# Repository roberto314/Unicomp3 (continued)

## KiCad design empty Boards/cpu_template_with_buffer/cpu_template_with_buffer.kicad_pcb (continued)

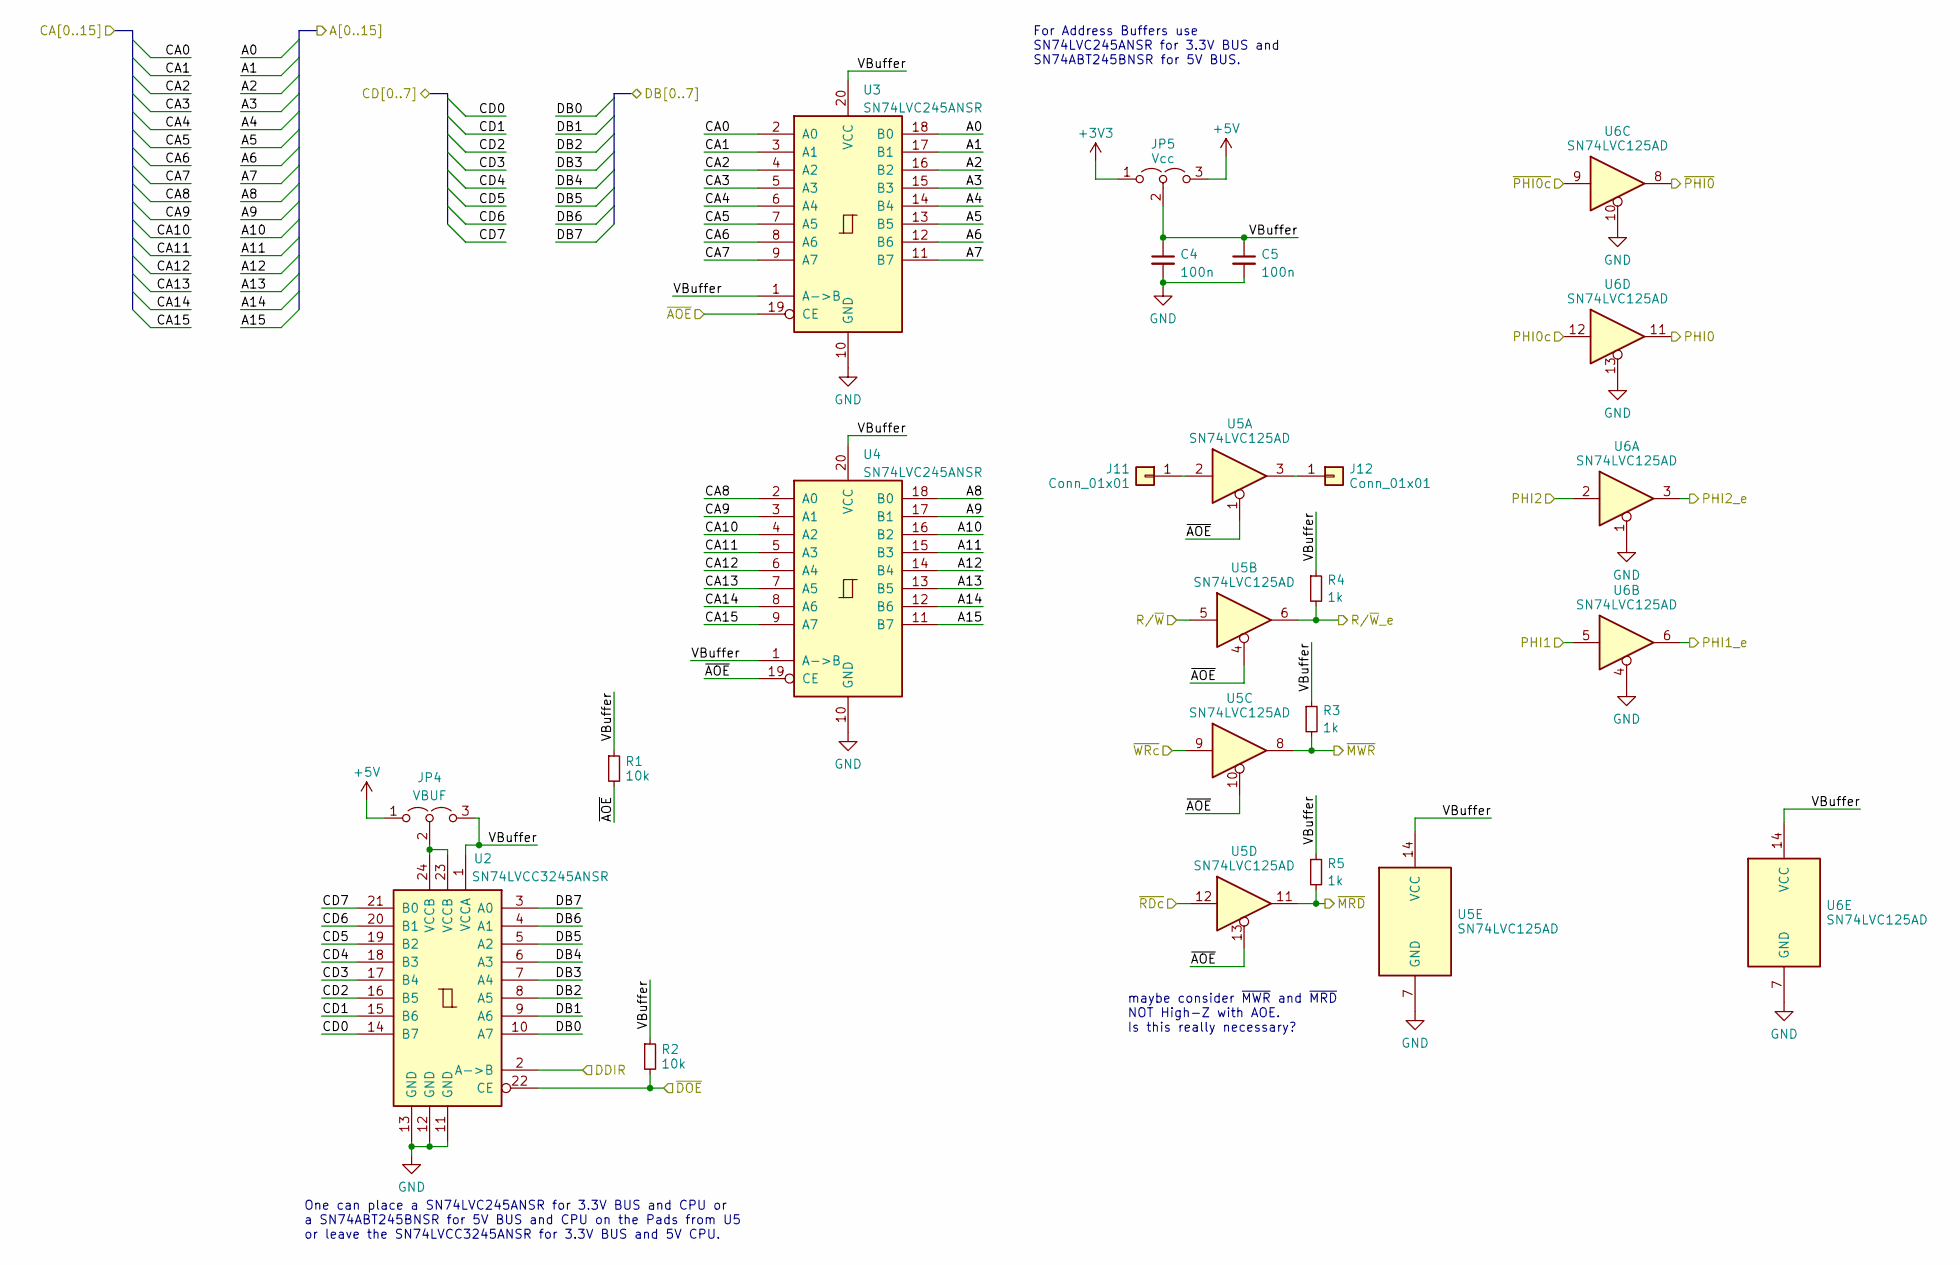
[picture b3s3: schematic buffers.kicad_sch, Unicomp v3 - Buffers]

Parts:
C4, C5: 100n; C_1206_3216Metric
J11, J12: Conn_01x01; PinHeader_1x01_P1.27mm_Vertical
JP4: VBUF; SolderJumper-3_P1.3mm_Open_Pad1.0x1.5mm_NumberLabels
JP5: Vcc; SolderJumper-3_P1.3mm_Open_RoundedPad1.0x1.5mm_NumberLabels
R1, R2: 10k; R_1206_3216Metric_Pad1.30x1.75mm_HandSolder
R3, R4, R5: 1k; R_1206_3216Metric_Pad1.30x1.75mm_HandSolder
U2: SN74LVCC3245ANSR; SO-24_5.3x15mm_P1.27mm
U3, U4: SN74LVC245ANSR; SO-20_5.3x12.6mm_P1.27mm
U5, U6: SN74LVC125AD; SOIC-14_3.9x8.7mm_P1.27mm

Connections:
+3V3: JP5.1 (A); also elsewhere on the board
+5V: JP4.1 (A), JP5.3 (B); also elsewhere on the board
/A0: U3.18 (B0); also elsewhere on the board
/A1: U3.17 (B1); also elsewhere on the board
/A2: U3.16 (B2); also elsewhere on the board
/A3: U3.15 (B3); also elsewhere on the board
/A4: U3.14 (B4); also elsewhere on the board
/A5: U3.13 (B5); also elsewhere on the board
/A6: U3.12 (B6); also elsewhere on the board
/A7: U3.11 (B7); also elsewhere on the board
/A8: U4.18 (B0); also elsewhere on the board
/A9: U4.17 (B1); also elsewhere on the board
/A10: U4.16 (B2); also elsewhere on the board
/A11: U4.15 (B3); also elsewhere on the board
/A12: U4.14 (B4); also elsewhere on the board
/A13: U4.13 (B5); also elsewhere on the board
/A14: U4.12 (B6); also elsewhere on the board
/A15: U4.11 (B7); also elsewhere on the board
/Buffers/PHI2: U6.2; also elsewhere on the board
/Buffers/VBuffer: C4.1, C5.1, JP4.3 (B), JP5.2 (C), R1.1, R2.1, R3.1, R4.1, R5.1, U2.1 (VCCA), U3.1 (A->B), U3.20 (VCC), U4.1 (A->B), U4.20 (VCC), U5.14 (VCC), U6.14 (VCC)
/CA0: U3.2 (A0)
/CA1: U3.3 (A1)
/CA2: U3.4 (A2)
/CA3: U3.5 (A3)
/CA4: U3.6 (A4)
/CA5: U3.7 (A5)
/CA6: U3.8 (A6)
/CA7: U3.9 (A7)
/CA8: U4.2 (A0)
/CA9: U4.3 (A1)
/CA10: U4.4 (A2)
/CA11: U4.5 (A3)
/CA12: U4.6 (A4)
/CA13: U4.7 (A5)
/CA14: U4.8 (A6)
/CA15: U4.9 (A7)
/CD0: U2.14 (B7)
/CD1: U2.15 (B6)
/CD2: U2.16 (B5)
/CD3: U2.17 (B4)
/CD4: U2.18 (B3)
/CD5: U2.19 (B2)
/CD6: U2.20 (B1)
/CD7: U2.21 (B0)
/CP1: U6.12; also elsewhere on the board
/CP2: U6.9; also elsewhere on the board
/CP31: R2.2, U2.22 (CE); also elsewhere on the board
/CP32: R1.2, U3.19 (CE), U4.19 (CE), U5.1, U5.4, U5.10, U5.13; also elsewhere on the board
/CP33: U5.9; also elsewhere on the board
/CP34: U5.12; also elsewhere on the board
/CP36: U5.5; also elsewhere on the board
/CP38: U6.5; also elsewhere on the board
/DB0: U2.10 (A7); also elsewhere on the board
/DB1: U2.9 (A6); also elsewhere on the board
/DB2: U2.8 (A5); also elsewhere on the board
/DB3: U2.7 (A4); also elsewhere on the board
/DB4: U2.6 (A3); also elsewhere on the board
/DB5: U2.5 (A2); also elsewhere on the board
/DB6: U2.4 (A1); also elsewhere on the board
/DB7: U2.3 (A0); also elsewhere on the board
/DDIR: U2.2 (A->B); also elsewhere on the board
/PH0: U6.11; also elsewhere on the board
/PHI1_e: U6.6; also elsewhere on the board
/PHI2_e: U6.3; also elsewhere on the board
/R/~W_e: R4.2, U5.6; also elsewhere on the board
/~MRD: R5.2, U5.11; also elsewhere on the board
/~MWR: R3.2, U5.8; also elsewhere on the board
/~PH0: U6.8; also elsewhere on the board
GND: C4.2, C5.2, U2.11 (GND), U2.12 (GND), U2.13 (GND), U3.10 (GND), U4.10 (GND), U5.7 (GND), U6.1, U6.4, U6.7 (GND), U6.10, U6.13; also elsewhere on the board
unnamed: J11.1, U5.2
unnamed: J12.1, U5.3
unnamed: JP4.2 (C), U2.23 (VCCB), U2.24 (VCCB)

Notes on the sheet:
For Address Buffers use SN74LVC245ANSR for 3.3V BUS and SN74ABT245BNSR for 5V BUS.
One can place a SN74LVC245ANSR for 3.3V BUS and CPU or a SN74ABT245BNSR for 5V BUS and CPU on the Pads from U5 or leave the SN74LVCC3245ANSR for 3.3V BUS and 5V CPU.
maybe consider ~{MWR} and ~{MRD} NOT High-Z with AOE. Is this really necessary?

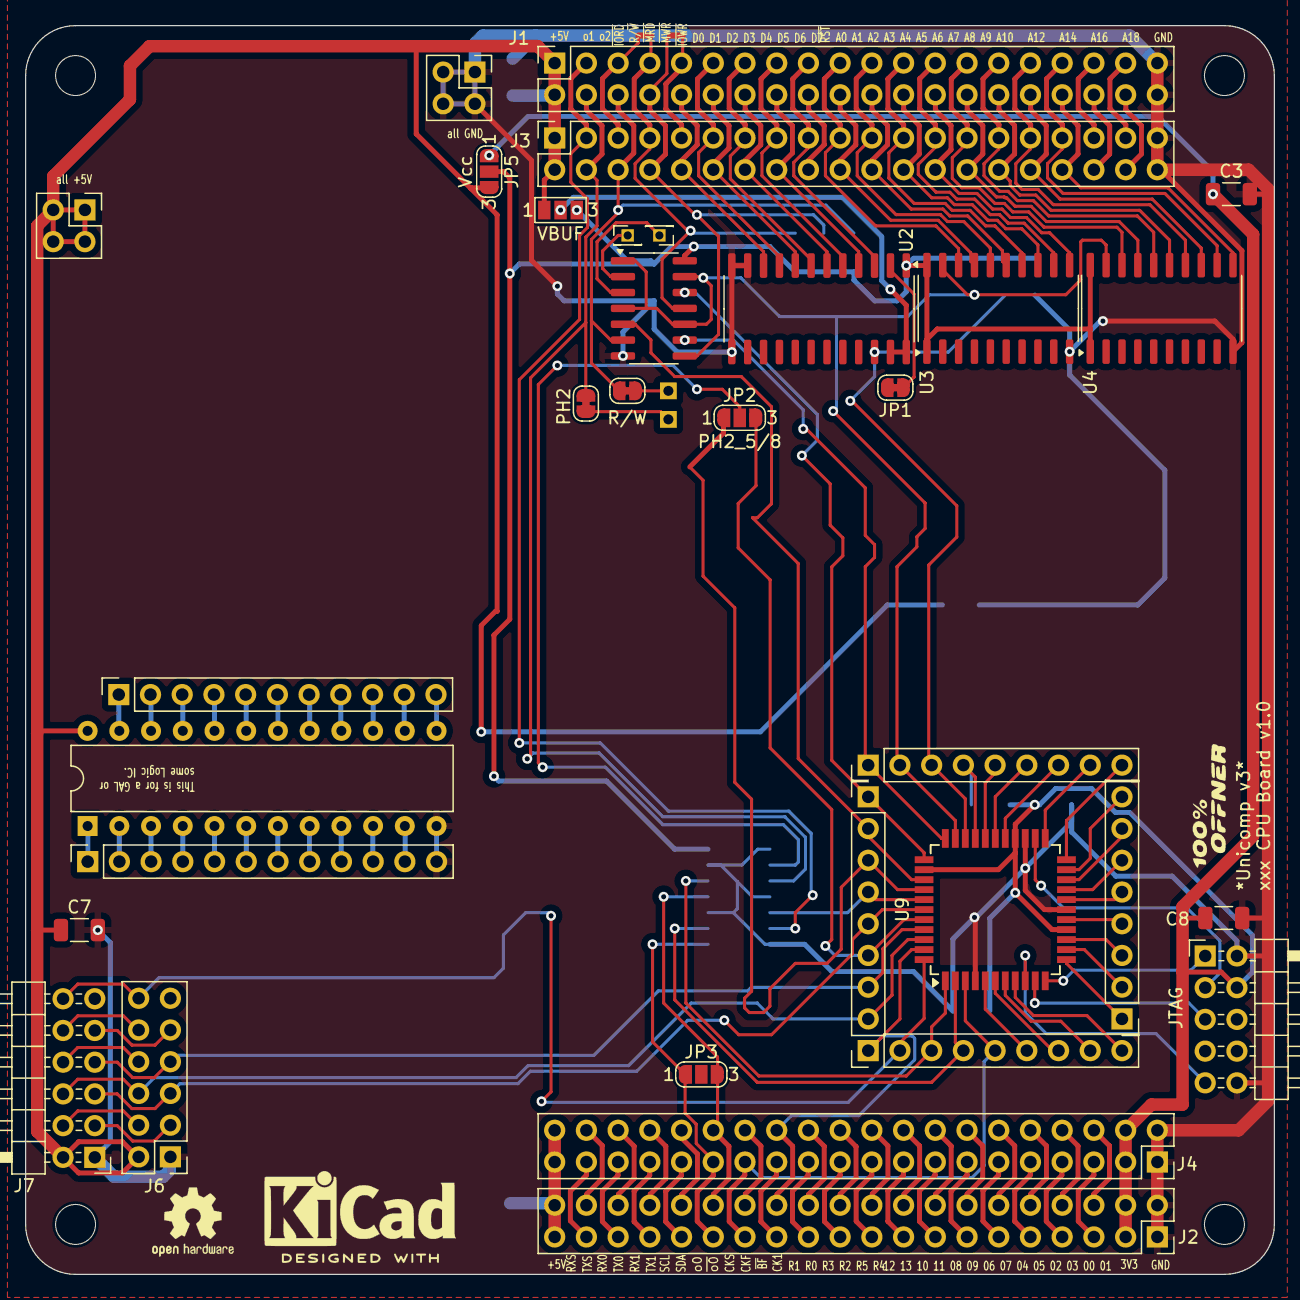
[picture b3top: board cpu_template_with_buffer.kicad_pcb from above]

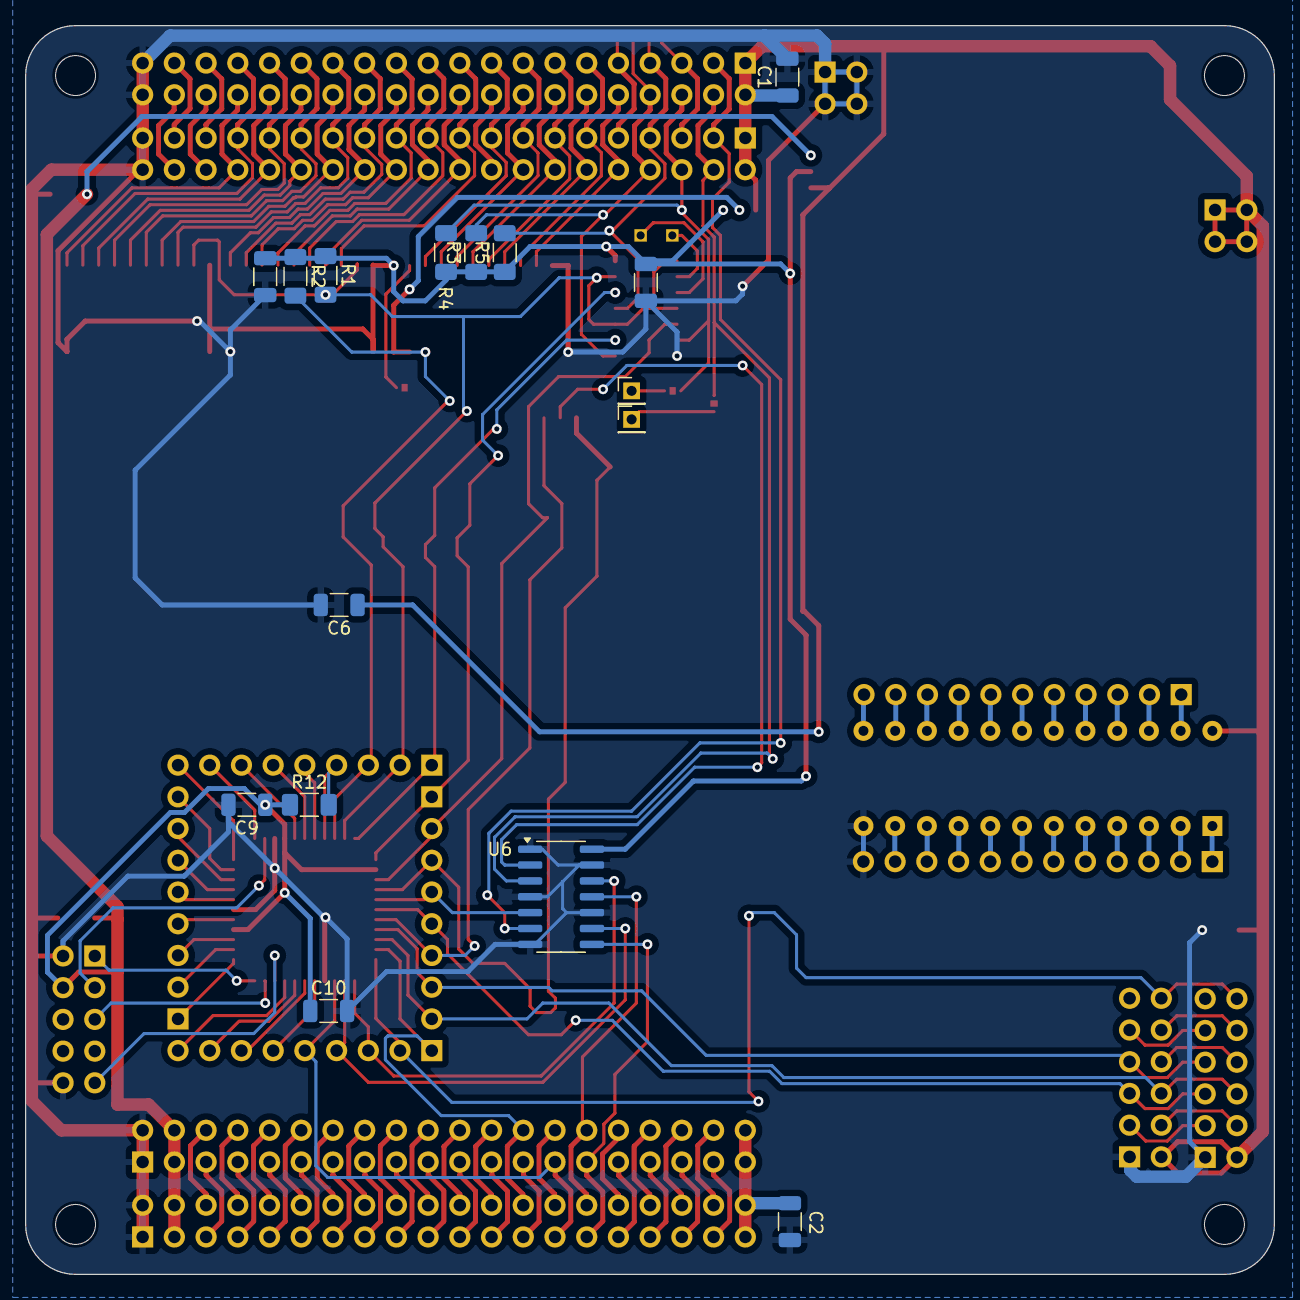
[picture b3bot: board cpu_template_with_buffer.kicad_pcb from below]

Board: 2 copper layers, 100.0 x 100.0 mm, 57 parts (16 on the bottom side), 144 nets.

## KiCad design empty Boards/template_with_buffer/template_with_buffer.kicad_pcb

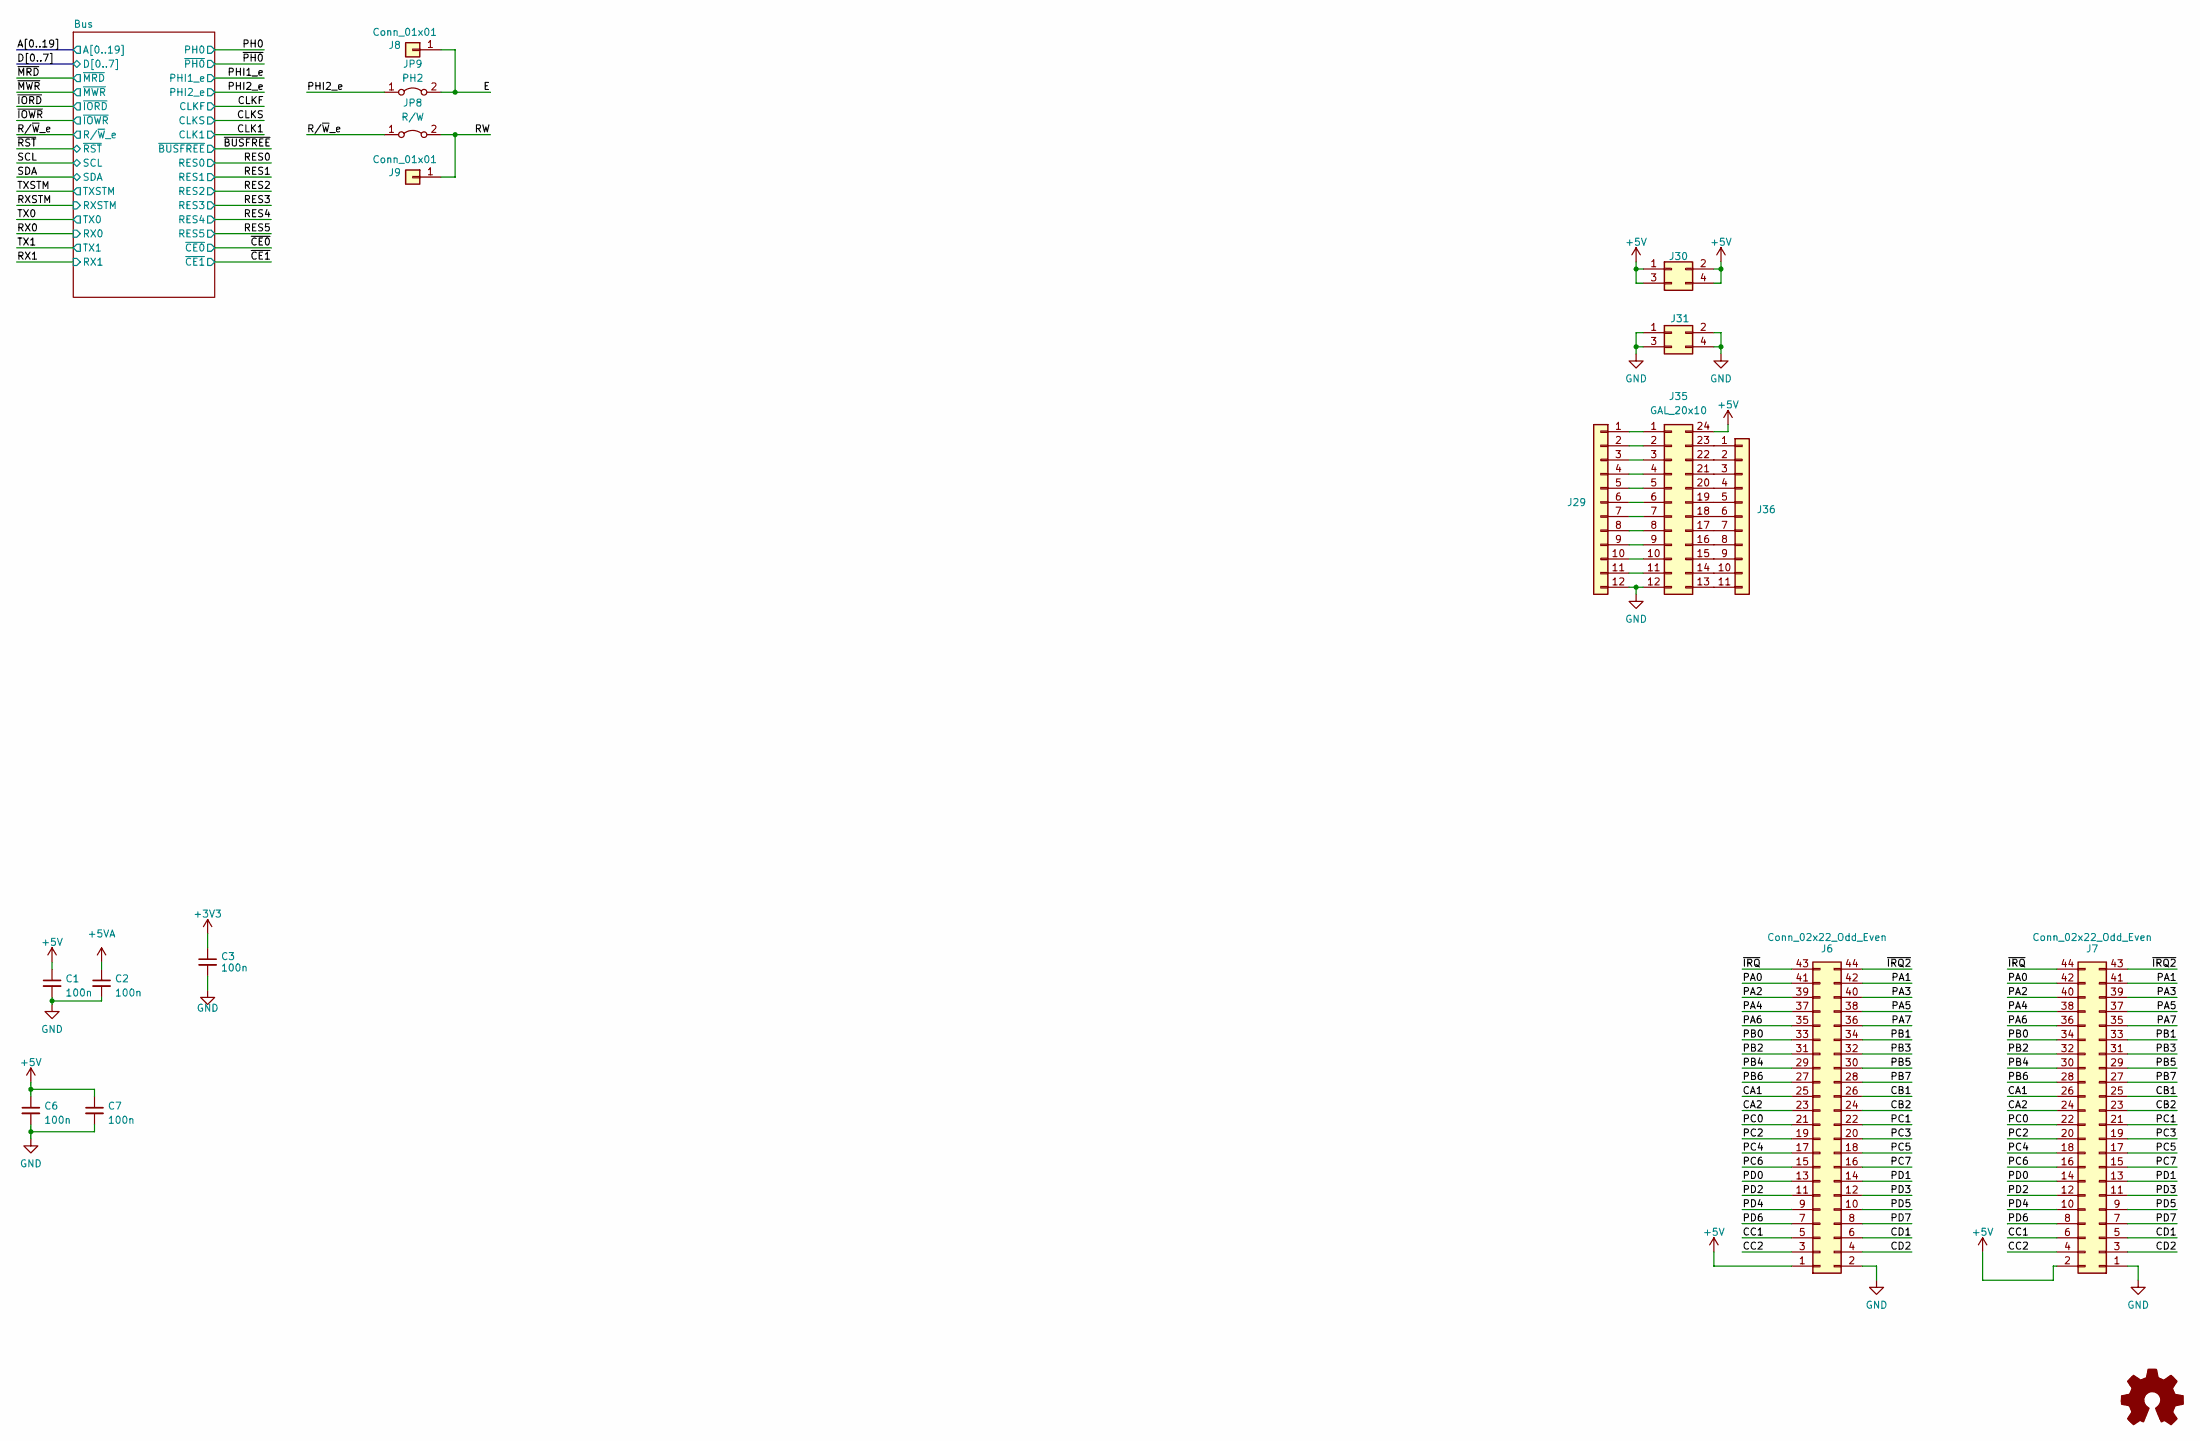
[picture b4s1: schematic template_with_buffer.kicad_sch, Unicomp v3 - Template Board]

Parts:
C1, C2, C3, C6, C7: 100n; C_1206_3216Metric
J6: Conn_02x22_Odd_Even; PinSocket_2x22_P2.54mm_Vertical
J7: Conn_02x22_Odd_Even; PinHeader_2x22_P2.54mm_Horizontal
J8, J9: Conn_01x01; PinHeader_1x01_P2.00mm_Vertical
J29: Conn_01x12; PinSocket_1x12_P2.54mm_Vertical
J30, J31: Conn_02x02_Odd_Even; PinSocket_2x02_P2.54mm_Vertical
J35: GAL_20x10; DIP-24_W7.62mm
J36: Conn_01x11; PinSocket_1x11_P2.54mm_Vertical
JP8: R/W; SolderJumper-2_P1.3mm_Bridged_RoundedPad1.0x1.5mm
JP9: PH2; SolderJumper-2_P1.3mm_Bridged_RoundedPad1.0x1.5mm

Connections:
+3V3: C3.1; also elsewhere on the board
+5V: C1.1, C6.1, C7.1, J6.1, J7.2, J30.1, J30.2, J30.3, J30.4, J35.24; also elsewhere on the board
+5VA: C2.1; also elsewhere on the board
/CA1: J6.25, J7.26
/CA2: J6.23, J7.24
/CB1: J6.26, J7.25
/CB2: J6.24, J7.23
/CC1: J6.5, J7.6
/CC2: J6.3, J7.4
/CD1: J6.6, J7.5
/CD2: J6.4, J7.3
/E: J8.1, JP9.2 (B)
/PA0: J6.41, J7.42
/PA1: J6.42, J7.41
/PA2: J6.39, J7.40
/PA3: J6.40, J7.39
/PA4: J6.37, J7.38
/PA5: J6.38, J7.37
/PA6: J6.35, J7.36
/PA7: J6.36, J7.35
/PB0: J6.33, J7.34
/PB1: J6.34, J7.33
/PB2: J6.31, J7.32
/PB3: J6.32, J7.31
/PB4: J6.29, J7.30
/PB5: J6.30, J7.29
/PB6: J6.27, J7.28
/PB7: J6.28, J7.27
/PC0: J6.21, J7.22
/PC1: J6.22, J7.21
/PC2: J6.19, J7.20
/PC3: J6.20, J7.19
/PC4: J6.17, J7.18
/PC5: J6.18, J7.17
/PC6: J6.15, J7.16
/PC7: J6.16, J7.15
/PD0: J6.13, J7.14
/PD1: J6.14, J7.13
/PD2: J6.11, J7.12
/PD3: J6.12, J7.11
/PD4: J6.9, J7.10
/PD5: J6.10, J7.9
/PD6: J6.7, J7.8
/PD7: J6.8, J7.7
/PHI2_e: JP9.1 (A); also elsewhere on the board
/RW: J9.1, JP8.2 (B)
/R/~W_e: JP8.1 (A); also elsewhere on the board
/~IRQ2: J6.44, J7.43
/~IRQ: J6.43, J7.44
GND: C1.2, C2.2, C3.2, C6.2, C7.2, J6.2, J7.1, J29.12, J31.1, J31.2, J31.3, J31.4, J35.12; also elsewhere on the board
unnamed: J29.1, J35.1
unnamed: J29.2, J35.2
unnamed: J29.3, J35.3
unnamed: J29.4, J35.4
unnamed: J29.5, J35.5
unnamed: J29.6, J35.6
unnamed: J29.7, J35.7
unnamed: J29.8, J35.8
unnamed: J29.9, J35.9
unnamed: J29.10, J35.10
unnamed: J29.11, J35.11
unnamed: J35.13, J36.11
unnamed: J35.14, J36.10
unnamed: J35.15, J36.9
unnamed: J35.16, J36.8
unnamed: J35.17, J36.7
unnamed: J35.18, J36.6
unnamed: J35.19, J36.5
unnamed: J35.20, J36.4
unnamed: J35.21, J36.3
unnamed: J35.22, J36.2
unnamed: J35.23, J36.1

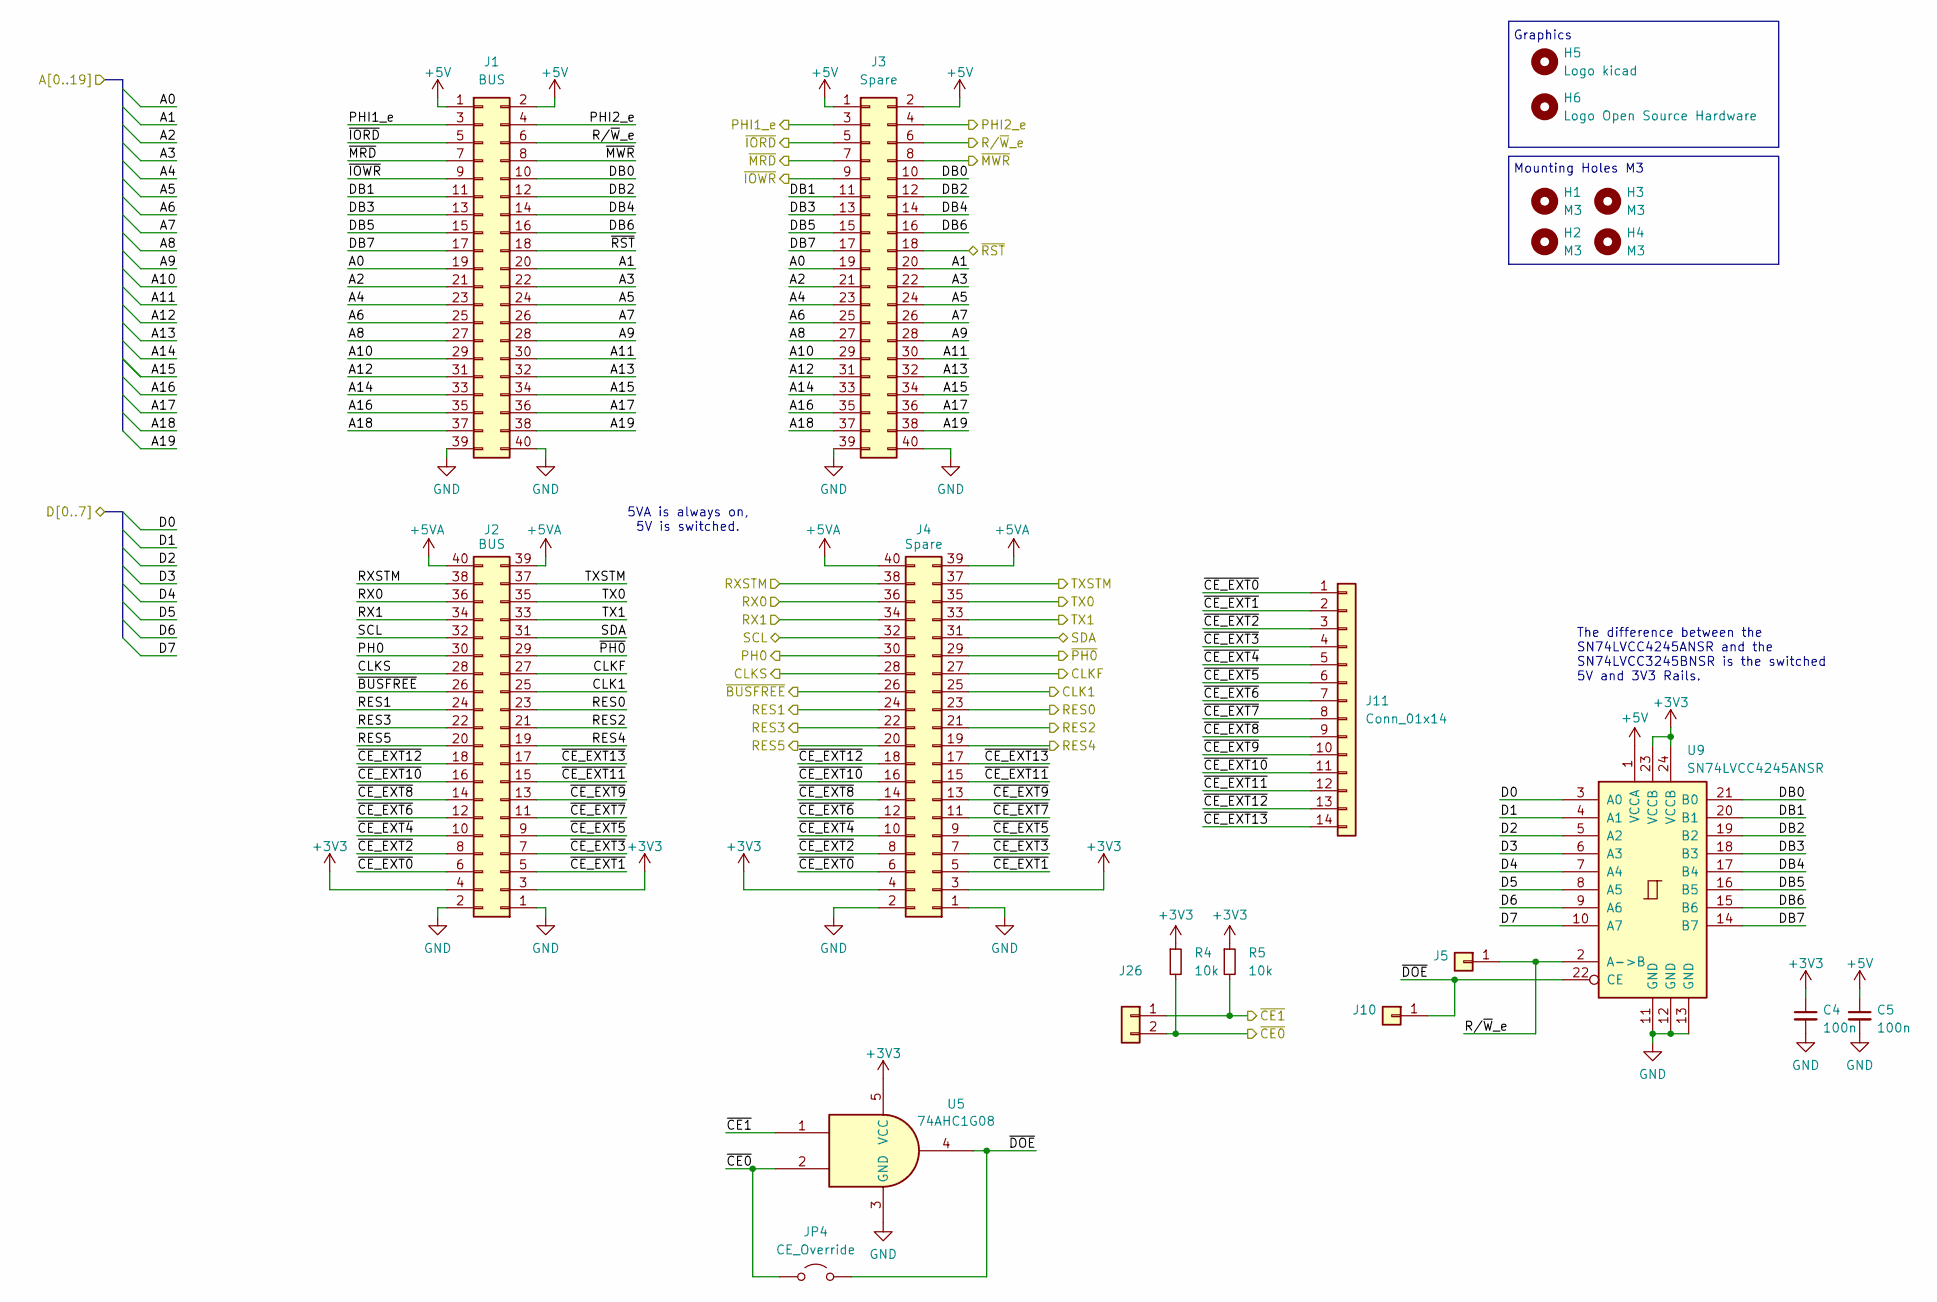
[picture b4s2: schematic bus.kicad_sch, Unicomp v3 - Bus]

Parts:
C4, C5: 100n; C_1206_3216Metric
H1, H2, H3, H4: M3; MountingHole_3.2mm_M3
H5: Logo kicad; KiCad-Logo2_6mm_SilkScreen
H6: Logo Open Source Hardware; OSHW-Logo2_7.3x6mm_SilkScreen
J1, J2: BUS; PinSocket_2x20_P2.54mm_Vertical
J3, J4: Spare; PinSocket_2x20_P2.54mm_Vertical
J5, J10: Conn_01x01; PinHeader_1x01_P2.00mm_Vertical
J11: Conn_01x14; PinSocket_1x14_P2.54mm_Vertical
J26: Conn_01x02; PinSocket_1x02_P2.54mm_Vertical
JP4: CE_Override; SolderJumper-2_P1.3mm_Open_RoundedPad1.0x1.5mm
R4, R5: 10k; R_1206_3216Metric_Pad1.30x1.75mm_HandSolder
U5: 74AHC1G08; SOT-23-5_HandSoldering
U9: SN74LVCC4245ANSR; SO-24_5.3x15mm_P1.27mm

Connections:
+3V3: C4.1, J2.3, J2.4, J4.3, J4.4, R4.1, R5.1, U5.5 (VCC), U9.23 (VCCB), U9.24 (VCCB); also elsewhere on the board
+5V: C5.1, J1.1, J1.2, J3.1, J3.2, U9.1 (VCCA); also elsewhere on the board
+5VA: J2.39, J2.40, J4.39, J4.40; also elsewhere on the board
/A0: J1.19, J3.19
/A1: J1.20, J3.20
/A2: J1.21, J3.21
/A3: J1.22, J3.22
/A4: J1.23, J3.23
/A5: J1.24, J3.24
/A6: J1.25, J3.25
/A7: J1.26, J3.26
/A8: J1.27, J3.27
/A9: J1.28, J3.28
/A10: J1.29, J3.29
/A11: J1.30, J3.30
/A12: J1.31, J3.31
/A13: J1.32, J3.32
/A14: J1.33, J3.33
/A15: J1.34, J3.34
/A16: J1.35, J3.35
/A17: J1.36, J3.36
/A18: J1.37, J3.37
/A19: J1.38, J3.38
/Bus/DB0: J1.10, J3.10, U9.21 (B0)
/Bus/DB1: J1.11, J3.11, U9.20 (B1)
/Bus/DB2: J1.12, J3.12, U9.19 (B2)
/Bus/DB3: J1.13, J3.13, U9.18 (B3)
/Bus/DB4: J1.14, J3.14, U9.17 (B4)
/Bus/DB5: J1.15, J3.15, U9.16 (B5)
/Bus/DB6: J1.16, J3.16, U9.15 (B6)
/Bus/DB7: J1.17, J3.17, U9.14 (B7)
/Bus/~CE_EXT0: J2.6, J4.6, J11.1
/Bus/~CE_EXT1: J2.5, J4.5, J11.2
/Bus/~CE_EXT2: J2.8, J4.8, J11.3
/Bus/~CE_EXT3: J2.7, J4.7, J11.4
/Bus/~CE_EXT4: J2.10, J4.10, J11.5
/Bus/~CE_EXT5: J2.9, J4.9, J11.6
/Bus/~CE_EXT6: J2.12, J4.12, J11.7
/Bus/~CE_EXT7: J2.11, J4.11, J11.8
/Bus/~CE_EXT8: J2.14, J4.14, J11.9
/Bus/~CE_EXT9: J2.13, J4.13, J11.10
/Bus/~CE_EXT10: J2.16, J4.16, J11.11
/Bus/~CE_EXT11: J2.15, J4.15, J11.12
/Bus/~CE_EXT12: J2.18, J4.18, J11.13
/Bus/~CE_EXT13: J2.17, J4.17, J11.14
/Bus/~DOE: J10.1, JP4.2 (B), U5.4, U9.22 (CE)
/CLK1: J2.25, J4.25
/CLKF: J2.27, J4.27
/CLKS: J2.28, J4.28
/D0: U9.3 (A0)
/D1: U9.4 (A1)
/D2: U9.5 (A2)
/D3: U9.6 (A3)
/D4: U9.7 (A4)
/D5: U9.8 (A5)
/D6: U9.9 (A6)
/D7: U9.10 (A7)
/PH0: J2.30, J4.30
/PHI1_e: J1.3, J3.3
/PHI2_e: J1.4, J3.4; also elsewhere on the board
/RES0: J2.23, J4.23
/RES1: J2.24, J4.24
/RES2: J2.21, J4.21
/RES3: J2.22, J4.22
/RES4: J2.19, J4.19
/RES5: J2.20, J4.20
/RX0: J2.36, J4.36
/RX1: J2.34, J4.34
/RXSTM: J2.38, J4.38
/R/~W_e: J1.6, J3.6, J5.1, U9.2 (A->B); also elsewhere on the board
/SCL: J2.32, J4.32
/SDA: J2.31, J4.31
/TX0: J2.35, J4.35
/TX1: J2.33, J4.33
/TXSTM: J2.37, J4.37
/~BUSFREE: J2.26, J4.26
/~CE0: J26.2, JP4.1 (A), R4.2, U5.2
/~CE1: J26.1, R5.2, U5.1
/~IORD: J1.5, J3.5
/~IOWR: J1.9, J3.9
/~MRD: J1.7, J3.7
/~MWR: J1.8, J3.8
/~PH0: J2.29, J4.29
/~RST: J1.18, J3.18
GND: C4.2, C5.2, J1.39, J1.40, J2.1, J2.2, J3.39, J3.40, J4.1, J4.2, U5.3 (GND), U9.11 (GND), U9.12 (GND), U9.13 (GND); also elsewhere on the board

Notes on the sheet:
Graphics
5VA is always on, 5V is switched.
Mounting Holes M3
The difference between the SN74LVCC4245ANSR and the SN74LVCC3245BNSR is the switched 5V and 3V3 Rails.

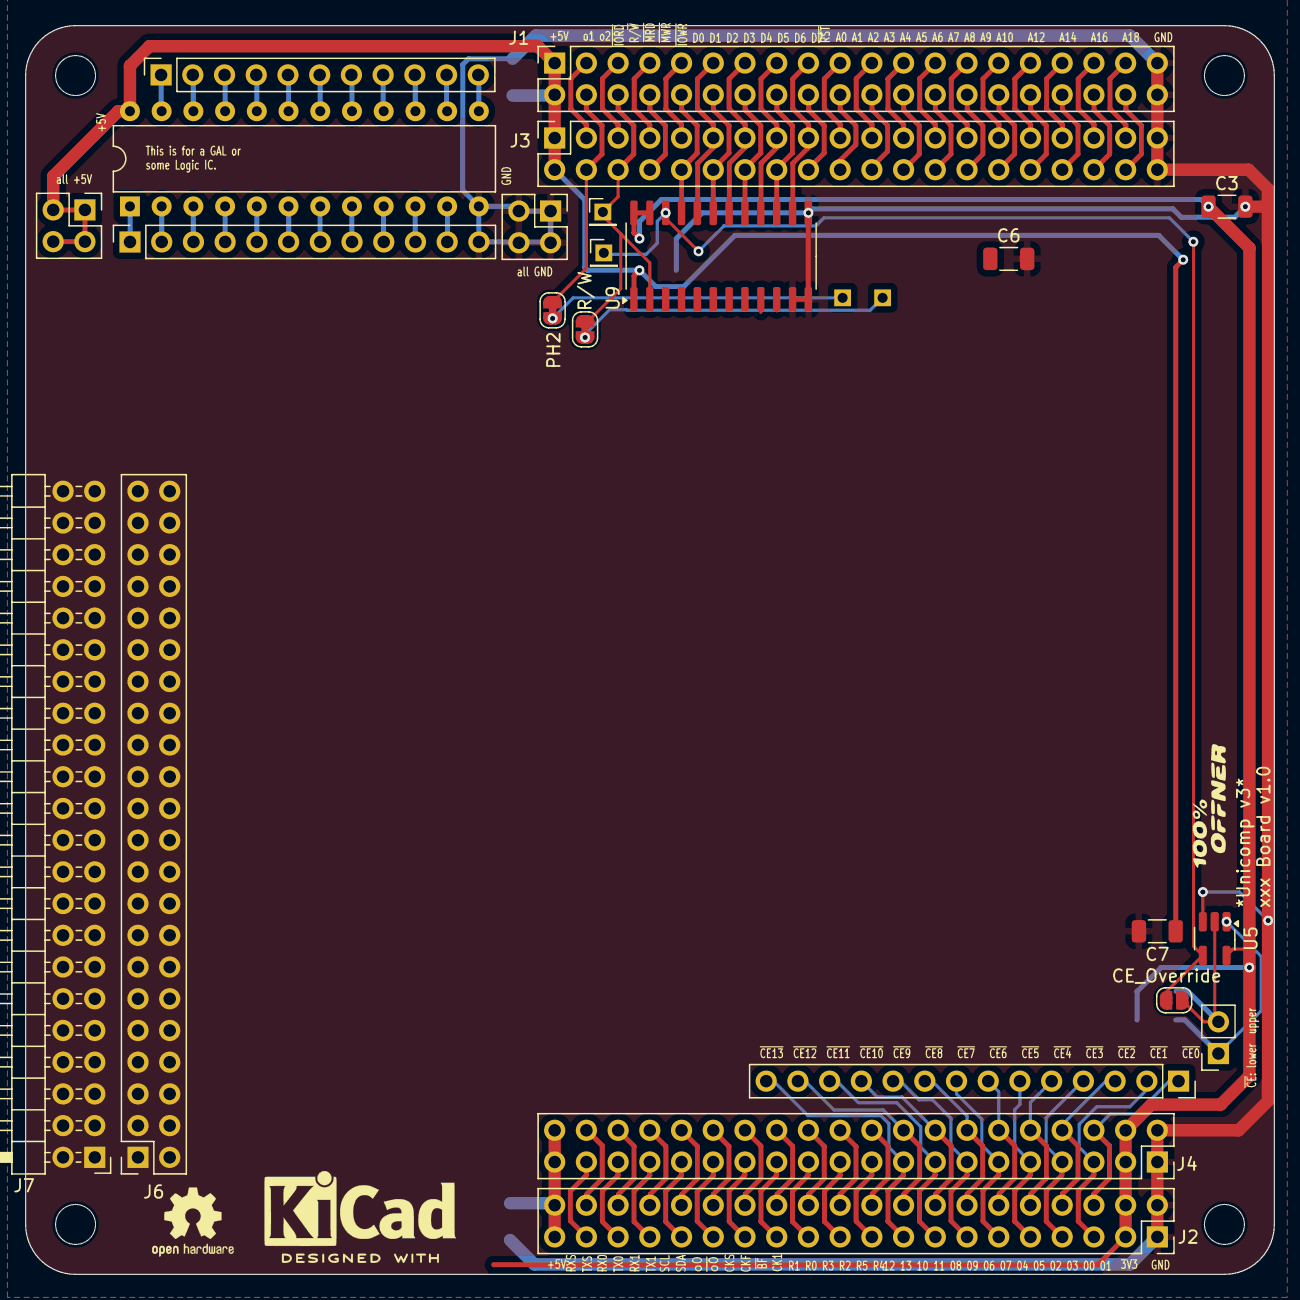
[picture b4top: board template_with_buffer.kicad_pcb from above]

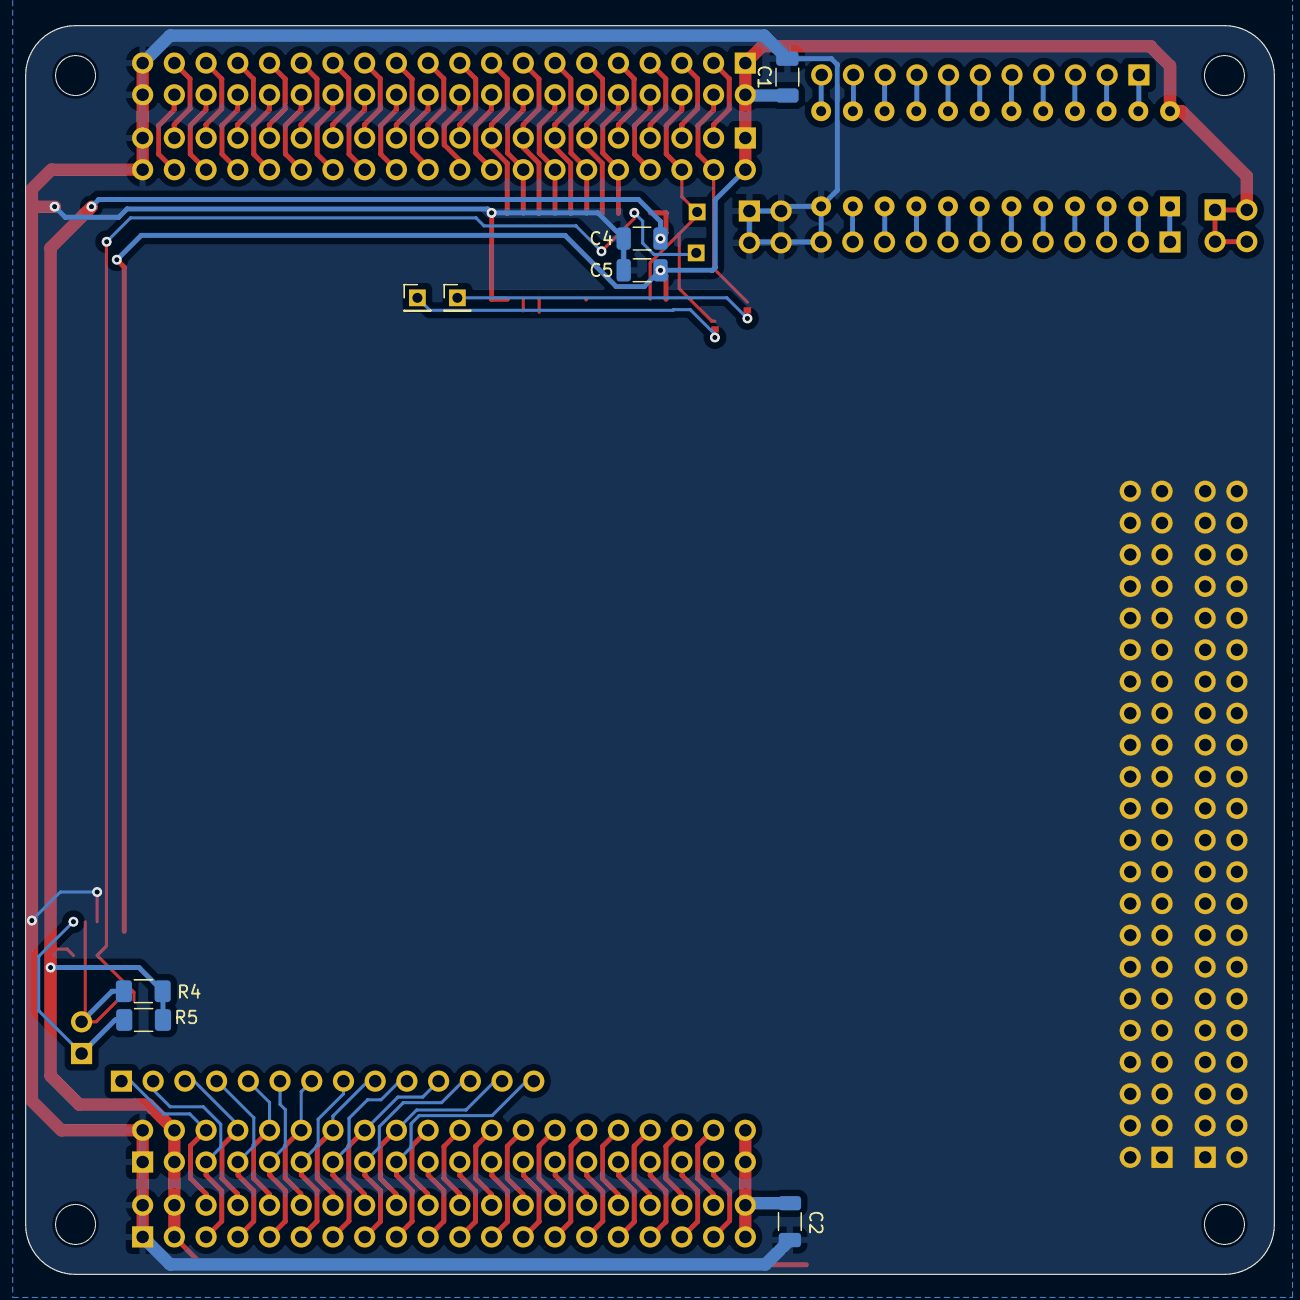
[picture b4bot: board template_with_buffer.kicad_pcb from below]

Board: 2 copper layers, 100.0 x 100.0 mm, 37 parts (8 on the bottom side), 143 nets.
